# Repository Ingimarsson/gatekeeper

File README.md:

# Gatekeeper

Gatekeeper is an access control system that can manage electrically controlled gates and doors with multiple mechanisms, for example RFID keypads, ALPR cameras, buttons and web portals.

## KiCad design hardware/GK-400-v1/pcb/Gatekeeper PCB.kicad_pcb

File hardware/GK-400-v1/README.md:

# GK-400v1

To write a program to the device:

 - Install Arduino IDE
 - Install libraries Ethernet2 and Wiegand (see zips in lib folder)
 - Write "ArduinoISP" program from examples to an Arduino Nano (we will use as a programmer)
 - Select programmer "Arduino as ISP" in IDE menu
 - Connect Arduino Nano to ISP pins on device, all pins are same but D10 (nano) to reset (device)
 - Arduino Nano reset must be pulled to ground when programming starts, and released after first timeout

Make sure fuses are correct, to use internal 8 MHz clock and brownout level 1:

    low 0xE2, high 0xD9, extended 0xFD

Set fuses (change avrdude paths):

    avrdude -Cavrdude.conf -v -V -patmega328p -cstk500v1 -P/dev/ttyUSB0 -b19200 -U lfuse:w:0xe2:m -U hfuse:w:0xd9:m -U efuse:w:0xfd:m

Make sure to give unique MAC address to each unit.

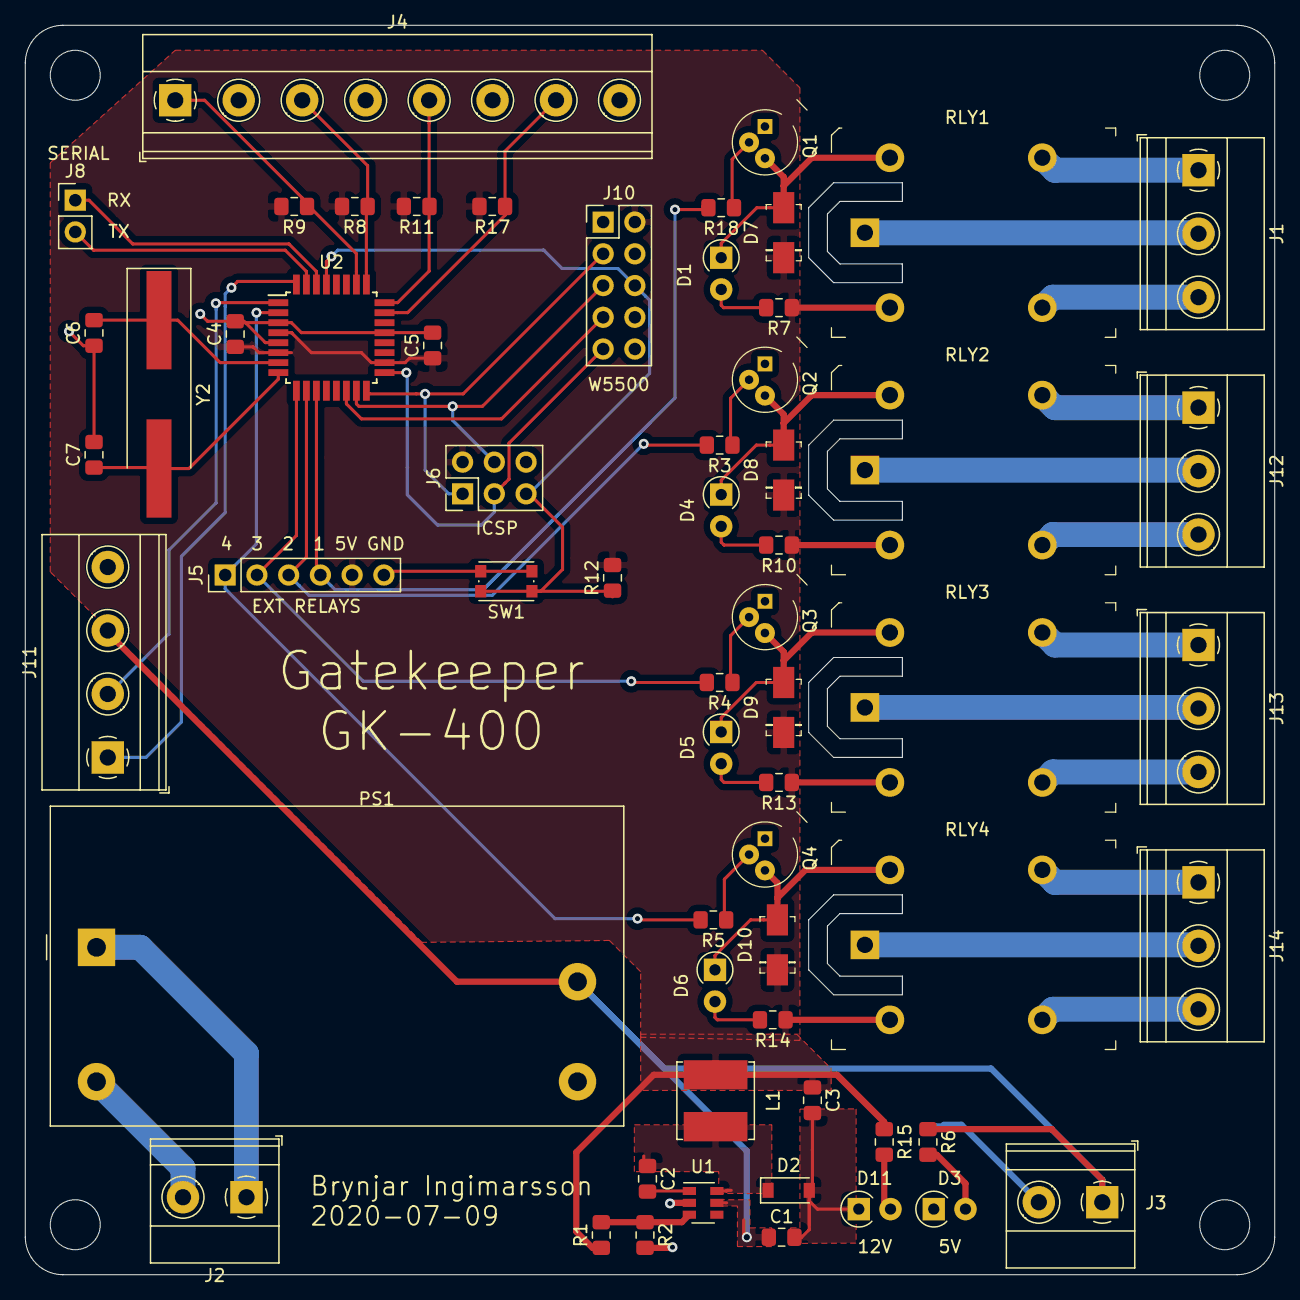
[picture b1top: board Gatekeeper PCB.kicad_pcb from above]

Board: 2 copper layers, 100.0 x 100.0 mm, 61 parts (0 on the bottom side), 53 nets.

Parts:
C1: 2.2uF 25V; C_0805_2012Metric_Pad1.15x1.40mm_HandSolder
C2, C4, C5: 100nF; C_0805_2012Metric_Pad1.15x1.40mm_HandSolder
C3: 10uF; C_0805_2012Metric_Pad1.15x1.40mm_HandSolder
C6, C7: 22pF; C_0805_2012Metric_Pad1.15x1.40mm_HandSolder
D1: RELAY1; D_A-405_P2.54mm_Vertical_AnodeUp
D2: MBR130T1G; D_SOD-123
D3: 12V; D_A-405_P2.54mm_Vertical_AnodeUp
D4: RELAY2; D_A-405_P2.54mm_Vertical_AnodeUp
D5: RELAY3; D_A-405_P2.54mm_Vertical_AnodeUp
D6: RELAY4; D_A-405_P2.54mm_Vertical_AnodeUp
D7, D8, D9, D10: S1G; DO-214AC
D11: 5V; D_A-405_P2.54mm_Vertical_AnodeUp
J1: RELAY1; TerminalBlock_Phoenix_MKDS-1,5-3-5.08_1x03_P5.08mm_Horizont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
J2: 230VAC IN; TerminalBlock_Phoenix_MKDS-1,5-2-5.08_1x02_P5.08mm_Horizont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
J3: 12VDC OUT; TerminalBlock_Phoenix_MKDS-1,5-2-5.08_1x02_P5.08mm_Horizont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
J4: Inputs; TerminalBlock_Phoenix_MKDS-1,5-8-5.08_1x08_P5.08mm_Horizont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
J5: EXT RLY; PinHeader_1x06_P2.54mm_Vertical
J6: ICSP; PinHeader_2x03_P2.54mm_Vertical
J8: Serial; PinHeader_1x02_P2.54mm_Vertical
J10: W5500 Shield; PinHeader_2x05_P2.54mm_Vertical
J11: WIEGAND; TerminalBlock_Phoenix_MKDS-1,5-4-5.08_1x04_P5.08mm_Horizont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
J12: RELAY2; TerminalBlock_Phoenix_MKDS-1,5-3-5.08_1x03_P5.08mm_Horizont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
J13: RELAY3; TerminalBlock_Phoenix_MKDS-1,5-3-5.08_1x03_P5.08mm_Horizont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
J14: RELAY4; TerminalBlock_Phoenix_MKDS-1,5-3-5.08_1x03_P5.08mm_Horizont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
L1: 22uH; L_Bourns_SRN6045TA
PS1: IRM-10-12; Converter_ACDC_MeanWell_IRM-10-xx_THT
Q1, Q2, Q3, Q4: 2N2222A; TO-18-3
R1: 54.9k; R_0805_2012Metric_Pad1.15x1.40mm_HandSolder
R2: 10k; R_0805_2012Metric_Pad1.15x1.40mm_HandSolder
R3, R4, R5, R8, R9, R11, R12, R17, R18: 1k; R_0805_2012Metric_Pad1.15x1.40mm_HandSolder
R6: 560; R_0805_2012Metric_Pad1.15x1.40mm_HandSolder
R7, R10, R13, R14, R15: 150; R_0805_2012Metric_Pad1.15x1.40mm_HandSolder
RLY1, RLY2, RLY3, RLY4: G5LE-14_DC5; Relay_THT_G5LE-14
SW1: Reset; SW_Push_1P1T_NO_CK_KMR2
U1: LMR16006YQ; SOT-23-6
U2: ATmega328P-AU; TQFP-32_7x7mm_P0.8mm
Y2: 16MHz; Crystal_SMD_HC49-SD_HandSoldering

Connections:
+5V: C3.1, C4.1, C5.1, D7.K, D8.K, D9.K, D10.K, J5.5, J6.2, J10.2, L1.1, R1.1, R7.1, R8.2, R9.2, R10.1, R11.2, R12.2, R13.1, R14.1, R15.1, R17.2, RLY1.2, RLY2.2, RLY3.2, RLY4.2, U2.4, U2.6, U2.18
+12V: C1.1, J3.1, J11.3, PS1.4, R6.1, U1.5
/INPUT1: J4.1, R9.1, U2.26
/INPUT2: J4.3, R8.1, U2.25
/INPUT3: J4.5, R11.1, U2.24
/INPUT4: J4.7, R17.1, U2.23
/MISO: J6.1, J10.3, U2.16
/MOSI: J6.4, J10.5, U2.15
/RELAY1: J5.4, R18.2, U2.11
/RELAY2: J5.3, R3.2, U2.10
/RELAY3: J5.2, R4.2, U2.9
/RELAY4: J5.1, R5.2, U2.2
/RST: J6.5, J10.6, R12.1, SW1.1, U2.29
/SCK: J6.3, J10.9, U2.17
/SS: J10.7, U2.14
/WIEGAND0: J11.1, U2.32
/WIEGAND1: J11.2, U2.1
GND: C1.2, C3.2, C4.2, C5.2, C6.1, C7.2, D2.2, D3.1, D11.1, J3.2, J4.2, J4.4, J4.6, J4.8, J5.6, J6.6, J10.4, J11.4, PS1.3, Q1.1, Q2.1, Q3.1, Q4.1, R2.2, SW1.2, U1.2, U2.3, U2.5, U2.21
unnamed: C2.1, D2.1, L1.2, U1.6
unnamed: C2.2, U1.1
unnamed: C6.2, U2.7, Y2.1
unnamed: C7.1, U2.8, Y2.2
unnamed: D1.1, D7.A, Q1.3, RLY1.5
unnamed: D1.2, R7.2
unnamed: D3.2, R6.2
unnamed: D4.1, D8.A, Q2.3, RLY2.5
unnamed: D4.2, R10.2
unnamed: D5.1, D9.A, Q3.3, RLY3.5
unnamed: D5.2, R13.2
unnamed: D6.2, R14.2
unnamed: D6.1, D10.A, Q4.3, RLY4.5
unnamed: D11.2, R15.2
unnamed: J1.1, RLY1.4
unnamed: J1.2, RLY1.1
unnamed: J1.3, RLY1.3
unnamed: J2.1, PS1.1
unnamed: J2.2, PS1.2
unnamed: J8.1, U2.30
unnamed: J8.2, U2.31
unnamed: J12.1, RLY2.4
unnamed: J12.2, RLY2.1
unnamed: J12.3, RLY2.3
unnamed: J13.1, RLY3.4
unnamed: J13.2, RLY3.1
unnamed: J13.3, RLY3.3
unnamed: J14.1, RLY4.4
unnamed: J14.2, RLY4.1
unnamed: J14.3, RLY4.3
unnamed: Q1.2, R18.1
unnamed: Q2.2, R3.1
unnamed: Q3.2, R4.1
unnamed: Q4.2, R5.1
unnamed: R1.2, R2.1, U1.3

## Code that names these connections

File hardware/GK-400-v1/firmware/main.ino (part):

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#include <EEPROM.h>
#include <avr/wdt.h>

#define RELAY1 4
#define RELAY2 5
#define RELAY3 6
#define RELAY4 7

#define BUTTON1 17
#define BUTTON2 16
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  Serial.begin(9600);
  Serial.println("Gatekeeper GK-400 v1 - Starting");

  pinMode(RELAY1, OUTPUT);  // relay 1
  pinMode(RELAY2, OUTPUT);  // relay 2
  pinMode(RELAY3, OUTPUT);  // relay 3
  pinMode(RELAY4, OUTPUT);  // relay 4
 
  // Register interrupt
  noInterrupts();
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
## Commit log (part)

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2020-06-06 Initialized backend skeleton with SQL models
2020-06-07 Added authentication endpoints
2020-06-07 Added Docker config
2020-06-07 Backend now (minimally) functional
2020-06-08 Added pages for frontend
2020-06-27 started working on stream manager
2020-06-28 added streaming functionality
2020-06-28 added openalpr directions, sensor_url and nvr trigger
2020-06-28 some frontend changes and nginx compose config
2020-06-29 added limit 50 results to activity endpoint
2020-06-29 added API communication and live stream to frontend
2020-07-15 started working on a GateService class
2020-07-27 added dev environment and got GateService working
2020-08-03 added auto restart when ffmpeg process reaches time limit
2020-08-03 activity page is more or less functional
2022-02-09 Add new Next.js frontend
2022-02-09 Add next-auth experiment and start working on mobile CSS
2022-02-10 Fix auth and mobile responsiveness
2022-02-10 Add Dockerfile and more
2022-02-22 Add skeleton for new streaming service
2022-02-23 Added daemon and config functionality for streaming service
2022-02-23 New streaming service fully functional
2022-02-24 Add fully functional streaming service with readme
2022-02-26 Add files for GK-400-v1 hardware
2022-02-26 Add MIT license
2022-03-02 Multiple updates and fixes for Next.js frontend
2022-03-02 Initialize new Flask backend with skeleton code
2022-03-02 Add alert_event table
2022-03-03 Add JWT and start implementing endpoints
2022-03-03 Add all alert endpoints
2022-03-03 Finish implementing all CRUD routes
2022-03-05 Add work on services and controller endpoints
2022-03-06 Update streaming service
2022-03-07 Final touch for backend MVP
2022-03-07 Working on docker configuration
2022-03-07 Move next-auth API route to /auth
2022-03-07 Add axios client and update docker config
2022-03-08 Add changes to get MVP running
2022-03-08 Fix streaming and controller statistics
2022-03-08 Add gate pages refresh every 5 seconds
2022-03-09 Add final additions to MVP demo
2022-03-09 Small fixes for MVP
2022-03-09 Fix OpenALPR and gatekeeper endpoints
2022-03-10 Fix statistics for gatekeeper
2022-03-10 Fix log creation for OpenALPR endpoint
2022-03-10 Fix authentication if deleted
2022-03-10 Fix incorrect endpoints for Gatekeeper module
2022-03-10 Add open command to gatekeeper endpoint
2022-03-10 Fix gatekeeper keypad opening
2022-03-10 Fix streaming service latest snapshot list
2022-03-14 Fix signout on 401 response
2022-03-14 Fix styled components SSR
2022-03-18 Fix models
2022-03-20 Add i18n support to frontend with partial IS translations
2022-03-20 Small translation fixes
2022-03-20 Added play and fullscreen to log entries and handling of incomplete snapshots
2022-03-20 Fix exception when invalid email tries to sign in
2022-03-20 Add saving of user language in backend
2022-03-20 Add jpeg preloading for log entry page
2022-03-20 Don't send sensitive codes to non admins
2022-03-20 Fix censoring of sensitive codes
2022-03-20 Hide admin buttons from non-admin users
2022-03-22 Return error if trying to add method with a code that exists
2022-03-22 Add image and nicer template to email alerts
2022-03-22 Fix deleting of old snapshots
2022-03-23 Rewrite access checking logic and add more detailed log results
2022-03-23 Add database migration
2022-03-23 Move camera streams into separate model
2022-03-24 Add websockets service and auto-refresh on new entry
2022-03-24 Minor fixes for new camera model
2022-03-24 Add config endpoints and auto-fetching external screens
2022-03-24 Small fixes of CSS and streaming service exception
2022-03-25 Add working monitor screen with number pad control
2022-03-25 Fix error with email attachment
2022-03-25 Correct port in docker compose
2022-04-22 Make websockets service less CPU hungry
2022-05-16 Add pagination to user methods and shorten history
2022-05-16 Add screenshot on hover in log records table
2022-05-17 Add anchors to user table
2022-05-17 Add error handling for cockpit external HTTP fetching
2022-05-17 Add setting to make confirm action modal optional
2022-05-17 Improve the design of cockpit mode
2022-05-17 Fix calling of gate HTTP trigger
2022-05-17 Fix 2 second delay when opening gate with keypad
2022-05-17 Add logging when sending command to controller fails
2022-05-17 Add method ID to response when creating a new method
2022-06-11 Fix bugs in firmware
2022-06-19 Make firmware more reliable
2022-07-24 Fix dir not found error in streaming service
2022-09-05 Add try/except to failing lines in streaming service
2022-09-07 Fix close gate bug when confirmation is disabled
2023-05-13 Add controller reset cause information
2023-05-20 Add sensor fault indicator in cloud and log free memory if hardware supports
2023-05-21 Fix error when multiple snapshots at same second
2023-05-21 Add support for method metadata
2023-05-21 Fix eslint errors
2023-06-27 Add new experimental ALPR reading method
2023-06-27 Add fixes for new experimental method
2023-06-27 Add ALPR view snapshots
2023-06-28 Add improvements to cockpit mode
2023-06-28 Add alpr_image field and observed reason for alpr_group results
2023-06-28 Add support for ALPR image stream and logs
2023-06-28 Add ALPR images to hover previews
2023-06-28 Add gap to hover images
2023-06-29 Add alpr_group handling logic with threshold
2023-06-29 Add more logic to alpr_group handling
2023-06-30 Use iframe url for external screens in cockpit
2023-11-24 Add WSS support, authentication on data dir, docker restart always
2023-11-24 Add reliability measures to firmware
2023-12-12 Add initial version for display communications
2023-12-12 Update matrix service for new display
2023-12-12 Update translations for frontend
2023-12-19 Fix issues with matrix implementation
2025-03-12 Add docs and libs to hardware directory
2025-05-16 Add bounding box feature for ALPR result
2026-03-16 Add some firmware fixex
